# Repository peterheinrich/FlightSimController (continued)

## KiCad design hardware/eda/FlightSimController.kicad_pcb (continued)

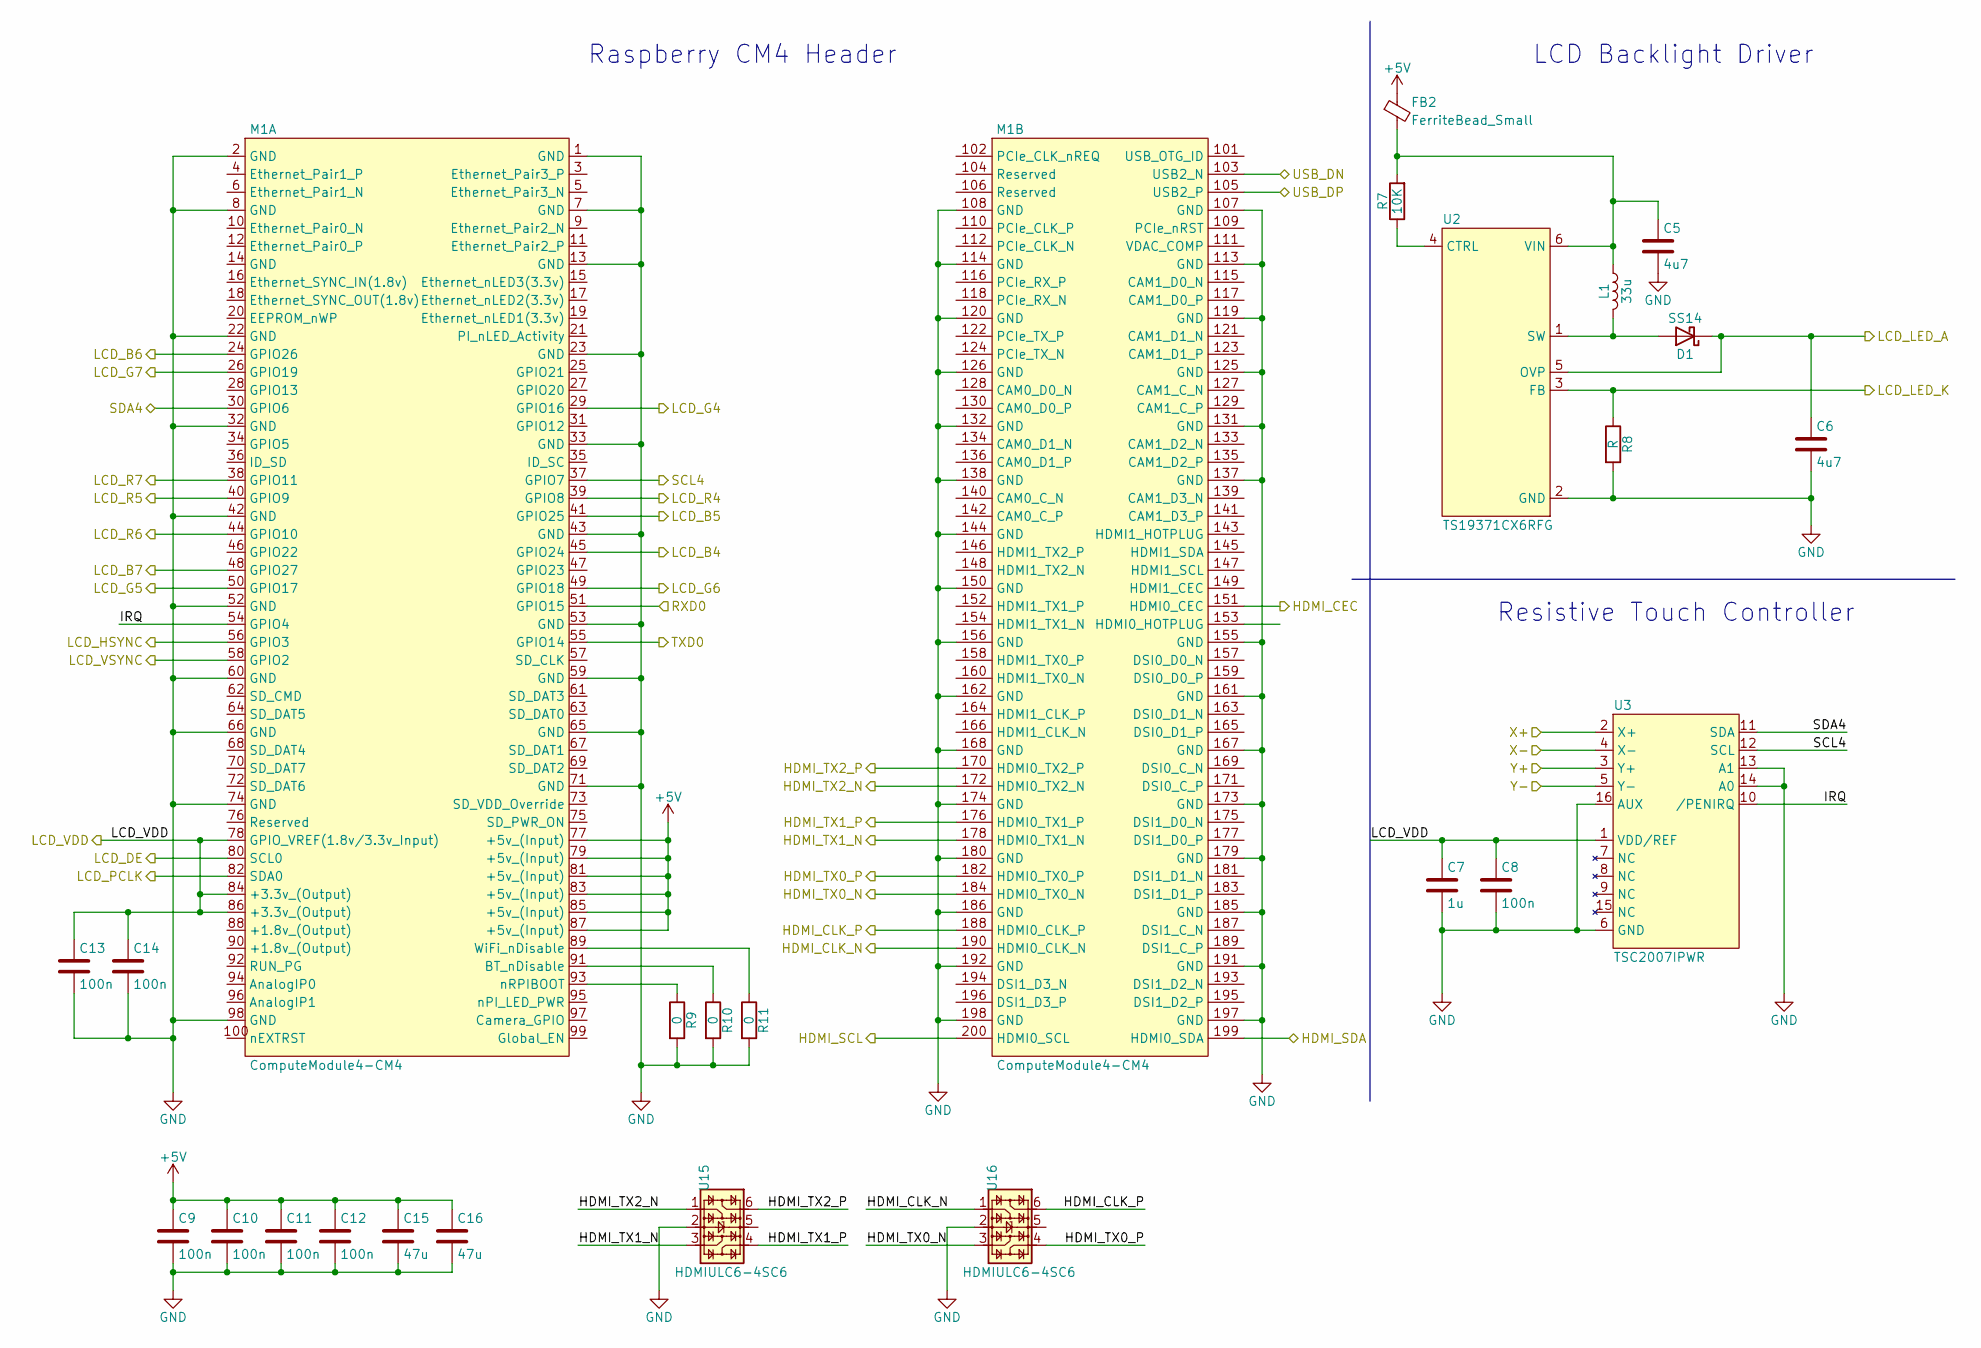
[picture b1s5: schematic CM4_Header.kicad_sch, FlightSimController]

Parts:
C5, C6: 4u7; C_0805_2012Metric_Pad1.18x1.45mm_HandSolder; MPN GRM21BR61H475KE51L
C7: 1u; C_0603_1608Metric_Pad1.08x0.95mm_HandSolder; MPN CC0603KRX5R6BB105
C8, C9, C10, C11, C12, C13, C14: 100n; C_0603_1608Metric_Pad1.08x0.95mm_HandSolder; MPN C0603C104K4RACTU
C15, C16: 47u; C_0805_2012Metric_Pad1.18x1.45mm_HandSolder; MPN GRM21BR61A476ME15L
D1: SS14; D_SMA_Handsoldering; MPN SS14-E3/61T
FB2: FerriteBead_Small; L_0805_2012Metric; MPN BLM21PG221SN1D
L1: 33u; L_Bourns-SRN4018; MPN SRN4018-330M
M1: ComputeModule4-CM4; Raspberry-Pi-4-Compute-Module; MPN DF40C-100DS-0.4V(51)
R7: 10K; R_0603_1608Metric_Pad0.98x0.95mm_HandSolder; MPN RC0603FR-0710KL
R8: R; R_1206_3216Metric_Pad1.30x1.75mm_HandSolder
R9, R10, R11: 0; R_0603_1608Metric_Pad0.98x0.95mm_HandSolder; MPN RC0603JR-070RL
U2: TS19371CX6RFG; SOT-23-6_Handsoldering; MPN TS19371CX6 RFG
U3: TSC2007IPWR; TSSOP-16_4.4x5mm_P0.65mm; MPN TSC2007IPWR
U15, U16: HDMIULC6-4SC6; SOT-23-6; MPN HDMIULC6-4SC6

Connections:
+5V: C9.1, C10.1, C11.1, C12.1, C15.1, C16.1, FB2.1, M1.77 (+5v_(Input)), M1.79 (+5v_(Input)), M1.81 (+5v_(Input)), M1.83 (+5v_(Input)), M1.85 (+5v_(Input)), M1.87 (+5v_(Input)); also elsewhere on the board
/B4: M1.45 (GPIO24); also elsewhere on the board
/B5: M1.41 (GPIO25); also elsewhere on the board
/B6: M1.24 (GPIO26); also elsewhere on the board
/B7: M1.48 (GPIO27); also elsewhere on the board
/CLK: M1.82 (SDA0); also elsewhere on the board
/CM4 Header/HDMI_CEC: M1.151 (HDMI0_CEC); also elsewhere on the board
/CM4 Header/HDMI_CLK_N: M1.190 (HDMI0_CLK_N), U16.1; also elsewhere on the board
/CM4 Header/HDMI_CLK_P: M1.188 (HDMI0_CLK_P), U16.6; also elsewhere on the board
/CM4 Header/HDMI_SCL: M1.200 (HDMI0_SCL); also elsewhere on the board
/CM4 Header/HDMI_SDA: M1.199 (HDMI0_SDA); also elsewhere on the board
/CM4 Header/HDMI_TX0_N: M1.184 (HDMI0_TX0_N), U16.3; also elsewhere on the board
/CM4 Header/HDMI_TX0_P: M1.182 (HDMI0_TX0_P), U16.4; also elsewhere on the board
/CM4 Header/HDMI_TX1_N: M1.178 (HDMI0_TX1_N), U15.3; also elsewhere on the board
/CM4 Header/HDMI_TX1_P: M1.176 (HDMI0_TX1_P), U15.4; also elsewhere on the board
/CM4 Header/HDMI_TX2_N: M1.172 (HDMI0_TX2_N), U15.1; also elsewhere on the board
/CM4 Header/HDMI_TX2_P: M1.170 (HDMI0_TX2_P), U15.6; also elsewhere on the board
/CM4 Header/IRQ: M1.54 (GPIO4), U3.10 (/PENIRQ)
/CM4 Header/RXD0: M1.51 (GPIO15); also elsewhere on the board
/CM4 Header/SCL4: M1.37 (GPIO7), U3.12 (SCL); also elsewhere on the board
/CM4 Header/SDA4: M1.30 (GPIO6), U3.11 (SDA); also elsewhere on the board
/CM4 Header/TXD0: M1.55 (GPIO14); also elsewhere on the board
/DE: M1.80 (SCL0); also elsewhere on the board
/G4: M1.29 (GPIO16); also elsewhere on the board
/G5: M1.50 (GPIO17); also elsewhere on the board
/G6: M1.49 (GPIO18); also elsewhere on the board
/G7: M1.26 (GPIO19); also elsewhere on the board
/HSYNC: M1.56 (GPIO3); also elsewhere on the board
/LCD_VDD: C7.1, C8.1, C13.1, C14.1, M1.78 (GPIO_VREF(1.8v/3.3v_Input)), M1.84 (+3.3v_(Output)), M1.86 (+3.3v_(Output)), U3.1 (VDD/REF); also elsewhere on the board
/LED_A: R8.1, U2.3 (FB); also elsewhere on the board
/LED_K: C6.1, D1.1 (K), U2.5 (OVP); also elsewhere on the board
/R4: M1.39 (GPIO8); also elsewhere on the board
/R5: M1.40 (GPIO9); also elsewhere on the board
/R6: M1.44 (GPIO10); also elsewhere on the board
/R7: M1.38 (GPIO11); also elsewhere on the board
/USB_D_N: M1.103 (USB2_N); also elsewhere on the board
/USB_D_P: M1.105 (USB2_P); also elsewhere on the board
/VSYNC: M1.58 (GPIO2); also elsewhere on the board
/X+: U3.2 (X+); also elsewhere on the board
/X-: U3.4 (X-); also elsewhere on the board
/Y+: U3.3 (Y+); also elsewhere on the board
/Y-: U3.5 (Y-); also elsewhere on the board
GND: C5.2, C6.2, C7.2, C8.2, C9.2, C10.2, C11.2, C12.2, C13.2, C14.2, C15.2, C16.2, M1.1 (GND), M1.2 (GND), M1.7 (GND), M1.8 (GND), M1.13 (GND), M1.22 (GND), M1.23 (GND), M1.32 (GND), M1.33 (GND), M1.42 (GND), M1.43 (GND), M1.52 (GND), M1.53 (GND), M1.59 (GND), M1.60 (GND), M1.65 (GND), M1.66 (GND), M1.71 (GND), M1.74 (GND), M1.98 (GND), M1.107 (GND), M1.108 (GND), M1.113 (GND), M1.114 (GND), M1.119 (GND), M1.120 (GND), M1.125 (GND), M1.126 (GND), M1.131 (GND), M1.132 (GND), M1.137 (GND), M1.138 (GND), M1.144 (GND), M1.150 (GND), M1.155 (GND), M1.156 (GND), M1.161 (GND), M1.162 (GND), M1.167 (GND), M1.168 (GND), M1.173 (GND), M1.174 (GND), M1.179 (GND), M1.180 (GND), M1.185 (GND), M1.186 (GND), M1.191 (GND), M1.192 (GND), M1.197 (GND), M1.198 (GND), R8.2, R9.2, R10.2, R11.2, U2.2 (GND), U3.6 (GND), U3.13 (A1), U3.14 (A0), U3.16 (AUX), U15.2, U16.2; also elsewhere on the board
unnamed: C5.1, FB2.2, L1.1, R7.2, U2.6 (VIN)
unnamed: D1.2 (A), L1.2, U2.1 (SW)
unnamed: M1.89 (WiFi_nDisable), R11.1
unnamed: M1.91 (BT_nDisable), R10.1
unnamed: M1.93 (nRPIBOOT), R9.1
unnamed: R7.1, U2.4 (CTRL)

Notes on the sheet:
LCD Backlight Driver
Raspberry CM4 Header
Resistive Touch Controller

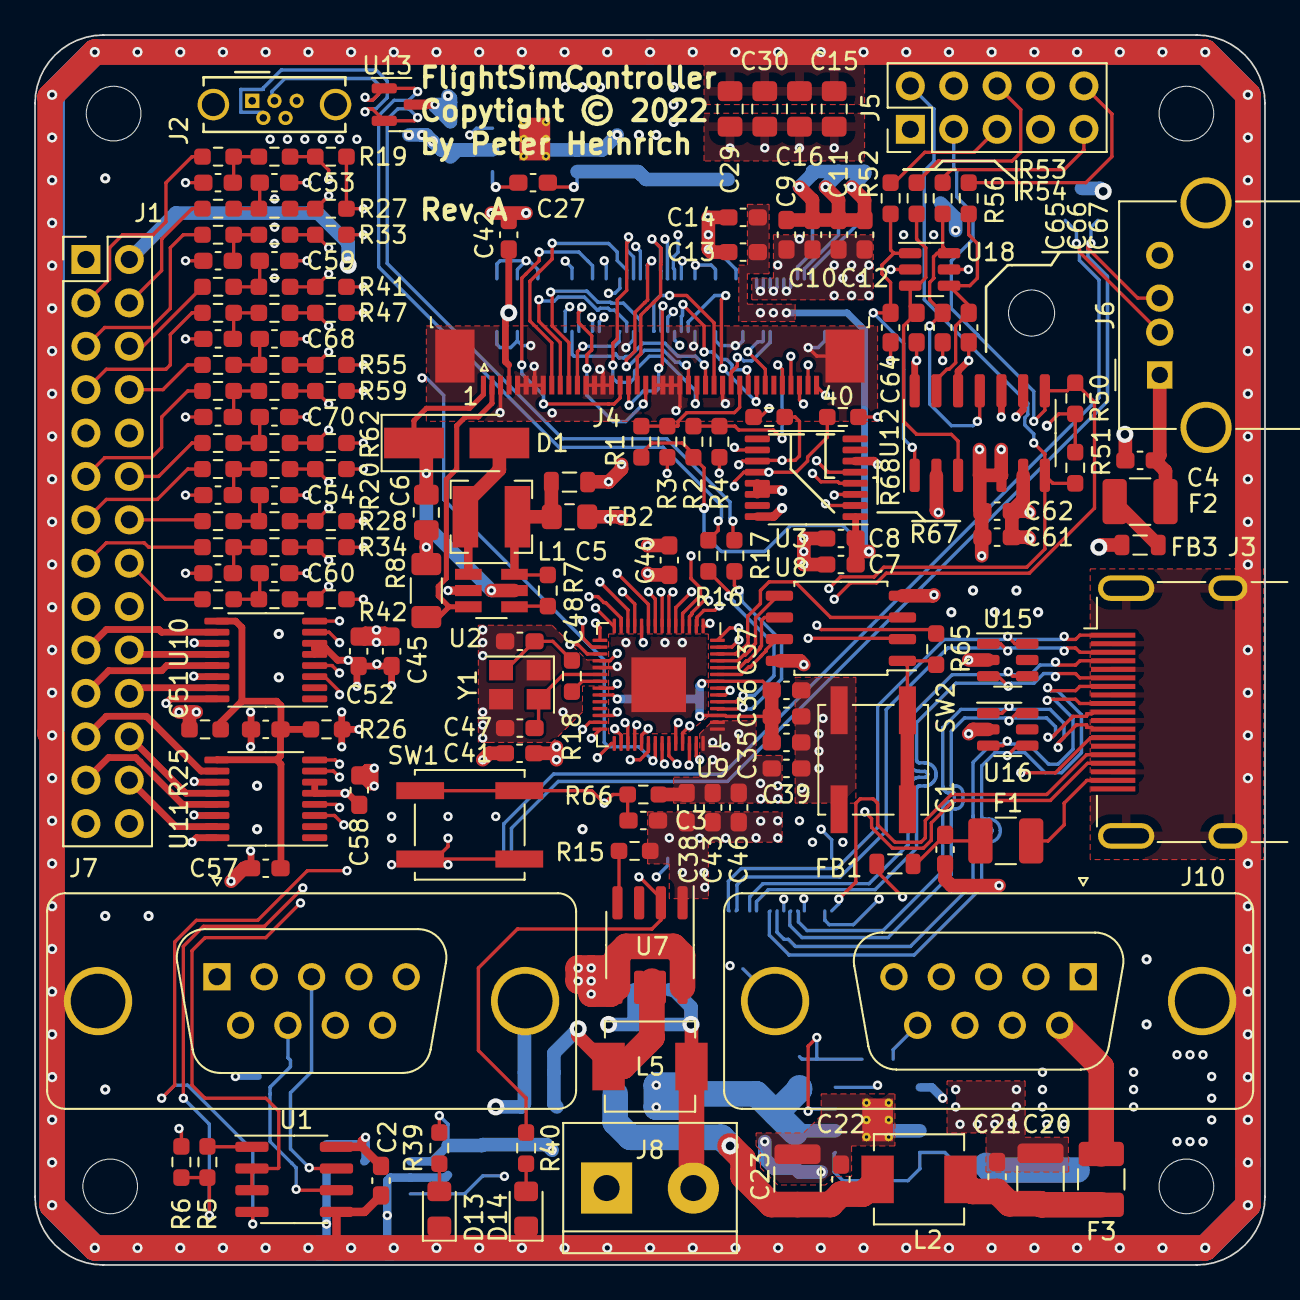
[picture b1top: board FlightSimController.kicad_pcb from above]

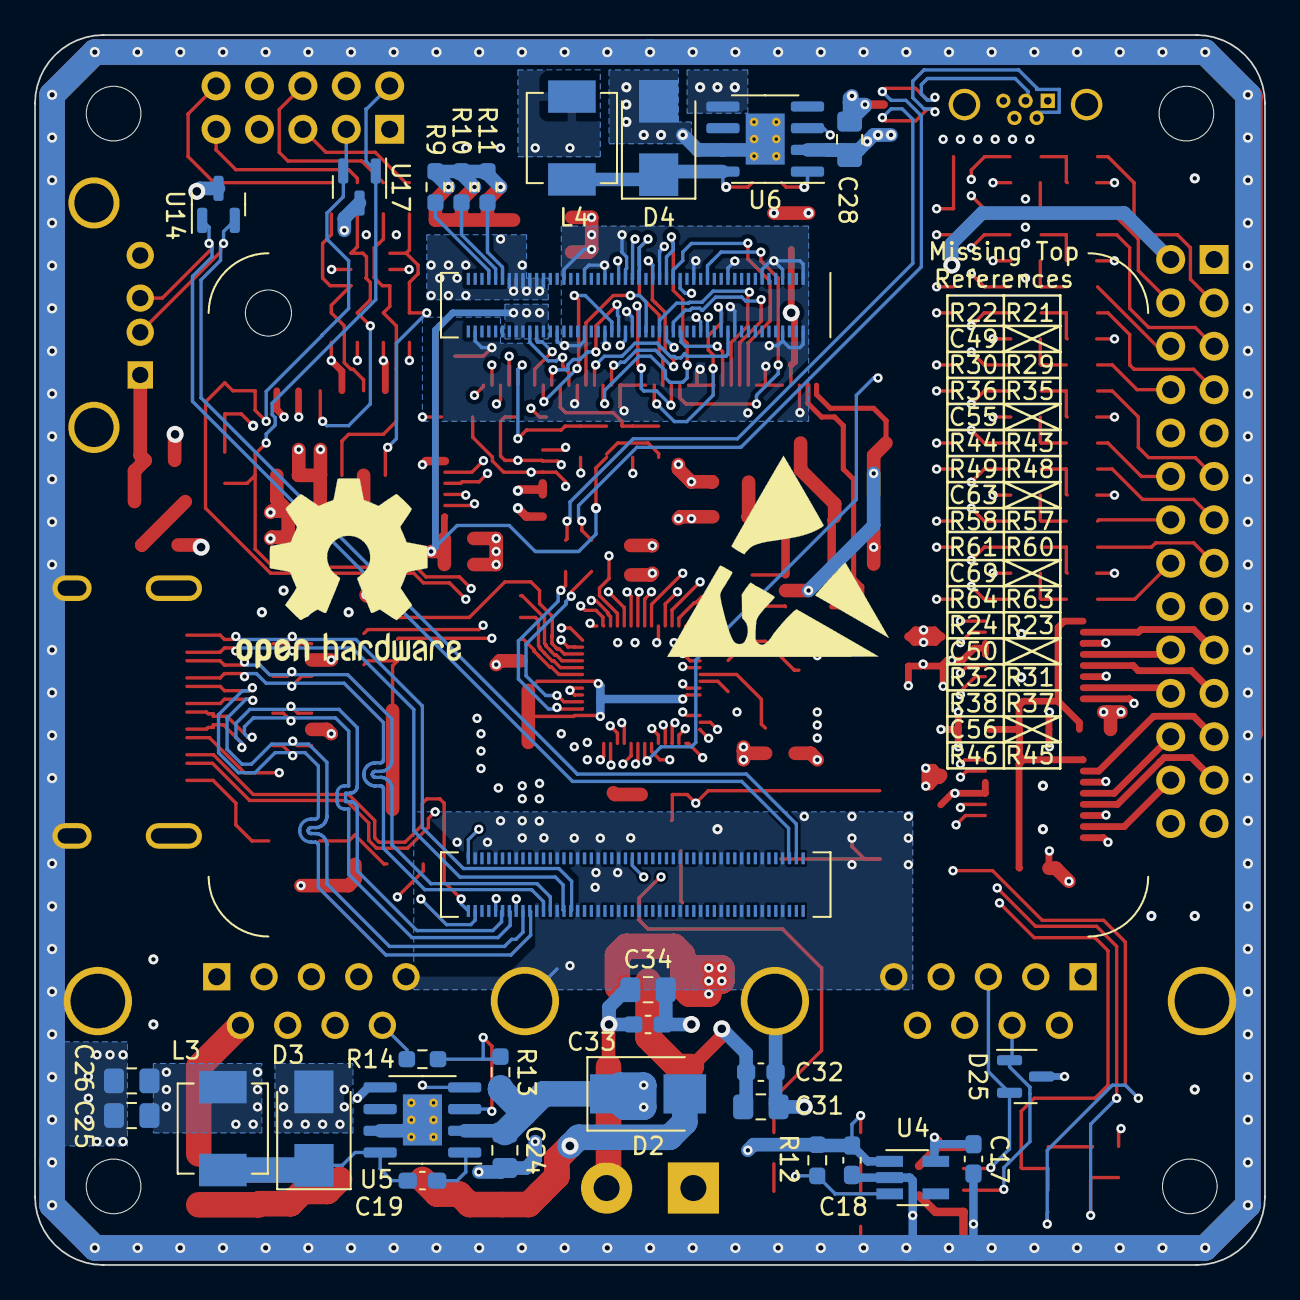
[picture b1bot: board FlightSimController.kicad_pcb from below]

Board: 6 copper layers, 72.0 x 72.0 mm, 190 parts (29 on the bottom side), 158 nets.

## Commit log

2022-12-06 Silkscreen Adjustments
2022-12-06 Deleting unused files
2022-12-06 Adapting .gitignore
2022-12-06 Updating Backlight Controller Sense Resistor
2022-12-06 Adding Procurement Ordering Information
2022-12-06 Removing DS_Store files :-(
2022-12-06 Updating Schematic
